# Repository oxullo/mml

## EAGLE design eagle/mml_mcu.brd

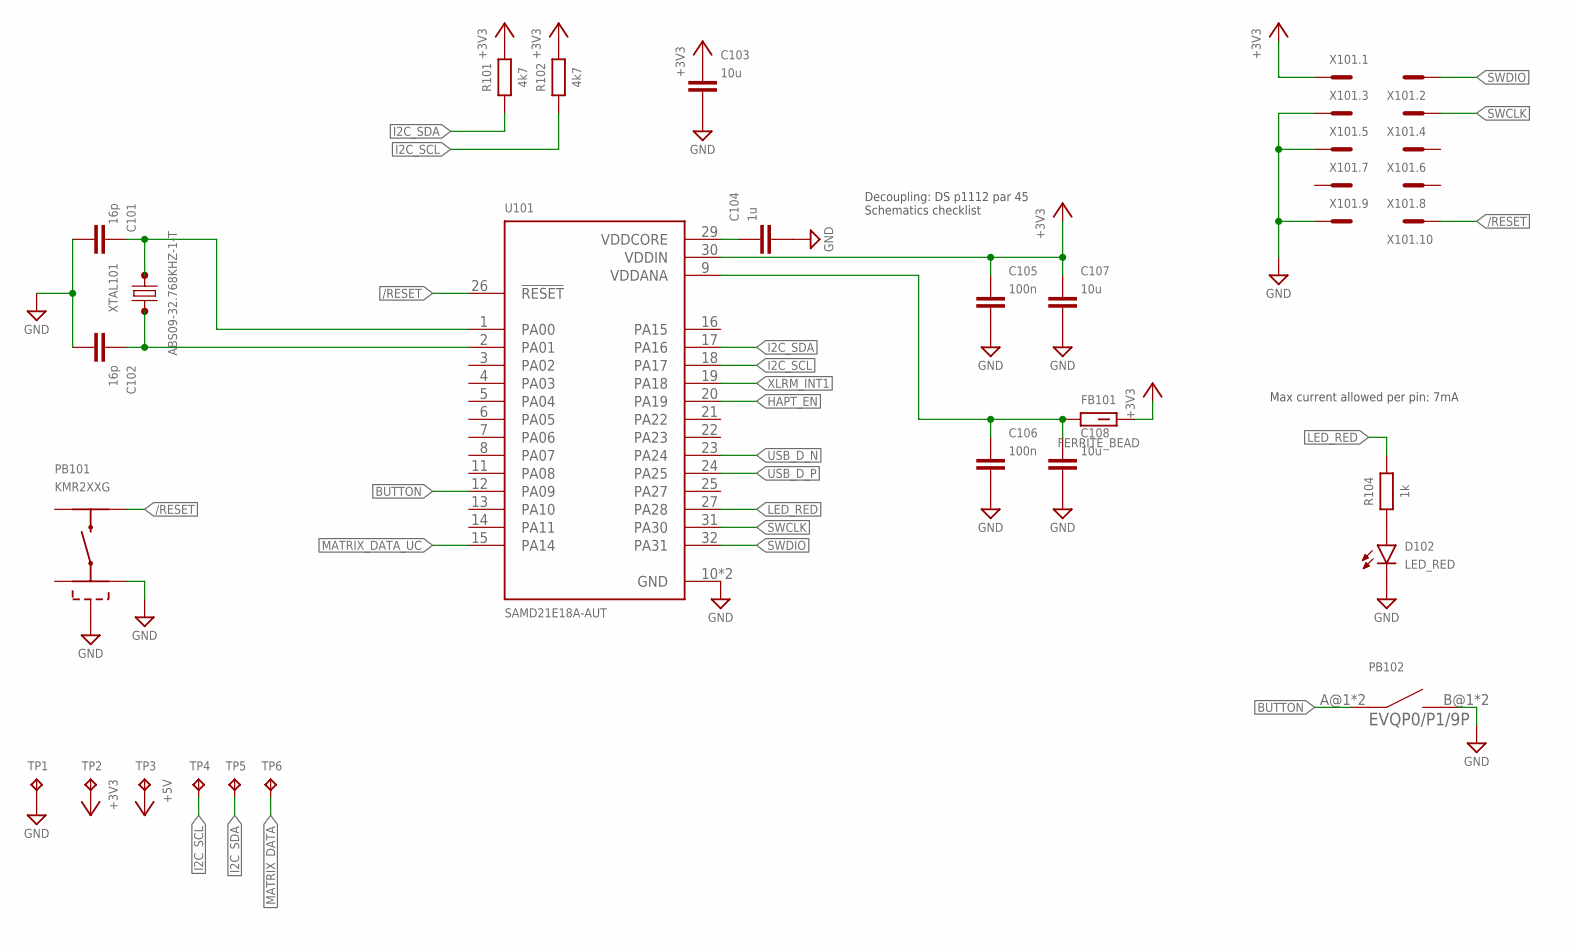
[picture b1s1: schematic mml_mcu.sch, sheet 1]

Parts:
C101, C102: 16p; CAPC1608X85
C103, C107, C108: 10u; CAPC2012X110
C104: 1u; CAPC1608X85
C105, C106: 100n; CAPC1608X85
D102: LED_RED; LEDC2012X110N_FLAT-R
FB101: FERRITE_BEAD; BEADC1608X95N
PB101: KMR2XXG
PB102: EVQP0/P1/9P
R101, R102: 4k7; RESC1608X60
R104: 1k; RESC1608X60
TP1, TP2, TP3, TP4, TP5, TP6: TPTP15R; TP15R
U101: SAMD21E18A-AUT; QFP80P900X900X120-32N
X101: M50-3600542R
XTAL101: ABS09-32.768KHZ-1-T; XTAL410X150X90

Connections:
+3V3: C103.1, C105.1, C107.1, FB101.2, R101.2, R102.2, TP2.TP, U101.30 (VDDIN), X101.1; also elsewhere on the board
+5V: TP3.TP; also elsewhere on the board
/RESET: PB101.1, U101.26 (!RESET), X101.10
BUTTON: PB102.A@1 (A), PB102.A@2 (A), U101.12 (PA09)
GND: C101.2, C102.2, C103.2, C104.2, C105.2, C106.2, C107.2, C108.2, D102.C, PB101.2, PB101.5, PB102.B@1 (B), PB102.B@2 (B), TP1.TP, U101.10 (GND), U101.28 (GND), X101.3, X101.5, X101.9; also elsewhere on the board
HAPT_EN: U101.20 (PA19); also elsewhere on the board
I2C_SCL: R102.1, TP4.TP, U101.18 (PA17); also elsewhere on the board
I2C_SDA: R101.1, TP5.TP, U101.17 (PA16); also elsewhere on the board
LED_RED: R104.2, U101.27 (PA28)
MATRIX_DATA: TP6.TP; also elsewhere on the board
MATRIX_DATA_UC: U101.15 (PA14); also elsewhere on the board
unnamed: C101.1, U101.1 (PA00), XTAL101.1 (A)
unnamed: C102.1, U101.2 (PA01), XTAL101.2 (B)
unnamed: C104.1, U101.29 (VDDCORE)
unnamed: D102.A, R104.1
unnamed: C106.1, C108.1, FB101.1, U101.9 (VDDANA)
SWCLK: U101.31 (PA30), X101.4
SWDIO: U101.32 (PA31), X101.2
USB_D_N: U101.23 (PA24); also elsewhere on the board
USB_D_P: U101.24 (PA25); also elsewhere on the board
XLRM_INT1: U101.19 (PA18); also elsewhere on the board

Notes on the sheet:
Decoupling: DS p1112 par 45 Schematics checklist
Max current allowed per pin: 7mA

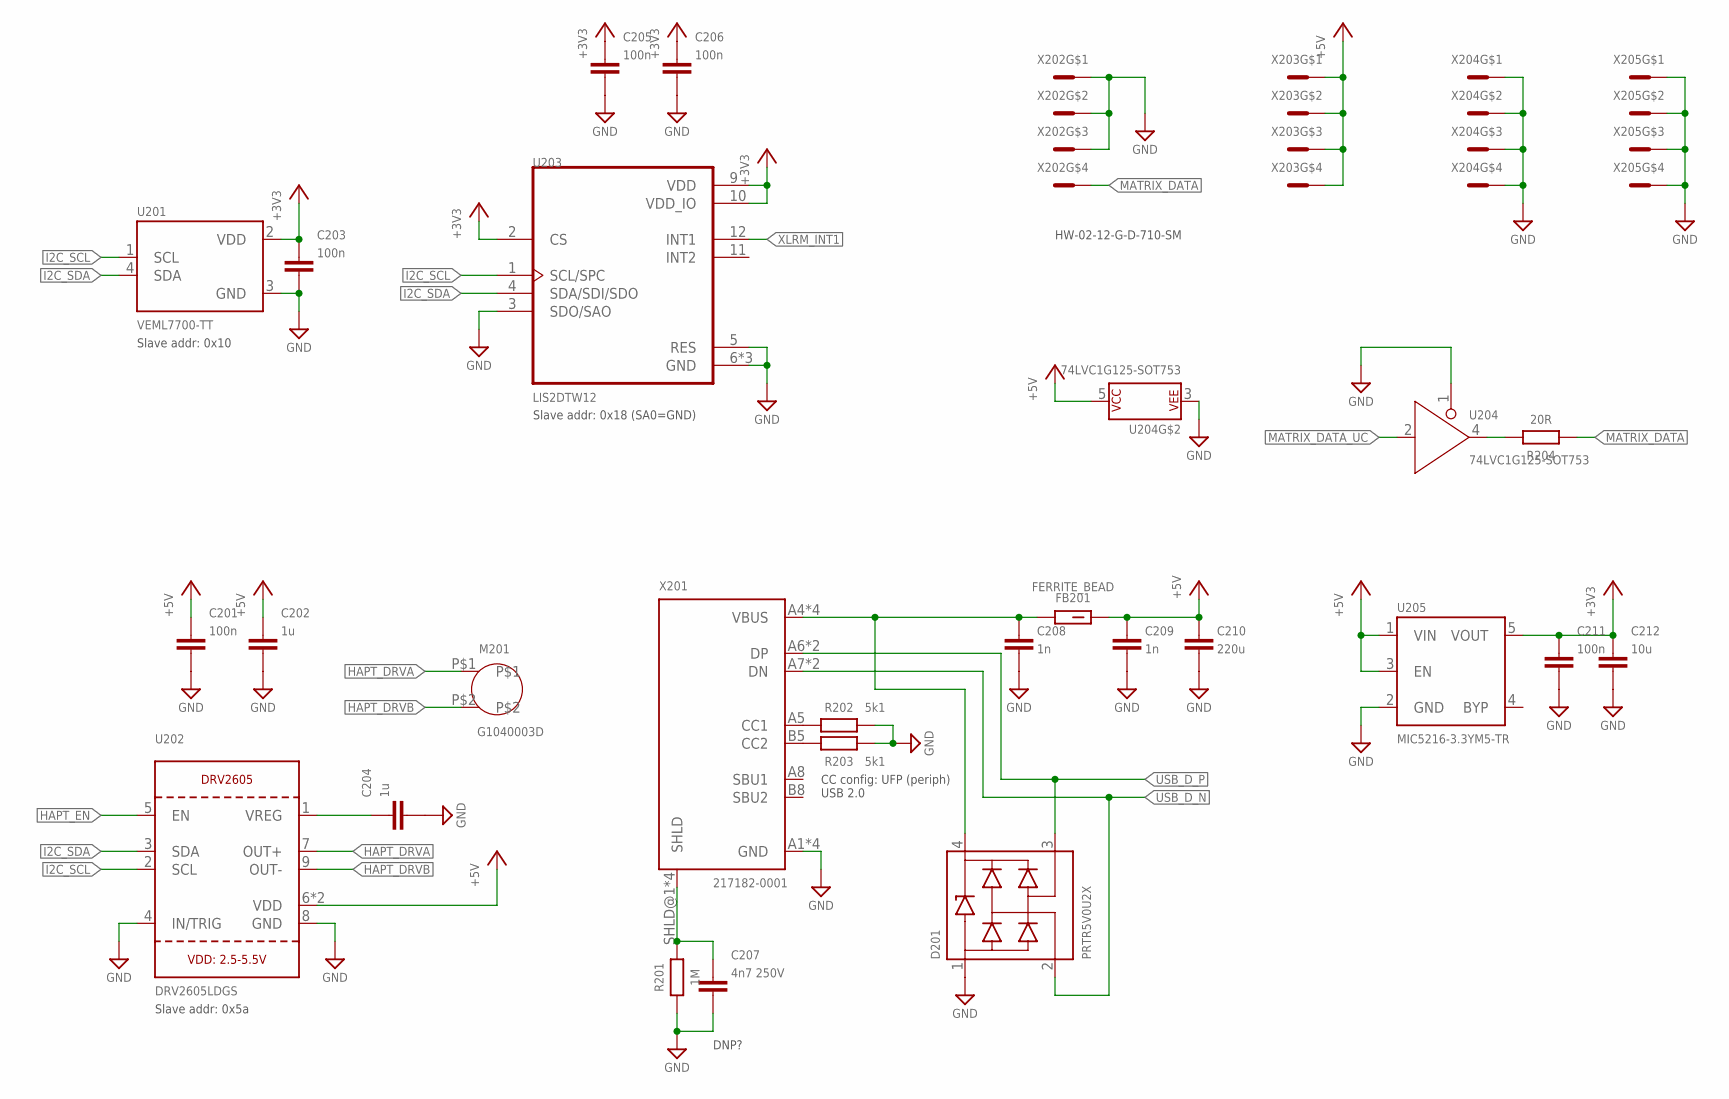
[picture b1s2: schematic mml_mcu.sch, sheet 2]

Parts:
C201, C203, C205, C206, C211: 100n; CAPC1608X85
C202, C204: 1u; CAPC1608X85
C207: 4n7 250V; CAPC1608X85
C208, C209: 1n; CAPC1608X85
C210: 220u; CAPC3216X135
C212: 10u; CAPC2012X110
D201: PRTR5V0U2X; SOT190P230X110-4N
FB201: FERRITE_BEAD; BEADC1608X95N
M201: G1040003D
R201: 1M; RESC1608X60
R202, R203: 5k1; RESC1608X60
R204: 20R; RESC1608X60
U201: VEML7700-TT; XDCR_VEML7700-TT
U202: DRV2605LDGS; PSOP10; LCSC_PART C527464
U203: LIS2DTW12; PQFN50P200X200100-12N; LCSC_PART C110926
U204: 74LVC1G125-SOT753; SOT95P280X145-5N
U205: MIC5216-3.3YM5-TR; SOT95P280X145-5N
X201: 217182-0001
X202, X203, X204, X205: HW-02-10-T-D-500-SM

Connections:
+3V3: C203.1, C205.1, C206.1, C211.1, C212.1, U201.2 (VDD), U203.2 (CS), U203.9 (VDD), U203.10 (VDD_IO), U205.5 (VOUT); also elsewhere on the board
+5V: C201.1, C202.1, C209.1, C210.1, FB201.2, U202.6 (VDD), U202.10 (VDD), U204.5 (P$V+), U205.1 (VIN), U205.3 (EN), X203.P$1, X203.P$2, X203.P$3, X203.P$4; also elsewhere on the board
GND: C201.2, C202.2, C203.2, C204.2, C205.2, C206.2, C207.2, C208.2, C209.2, C210.2, C211.2, C212.2, D201.1, R201.1, R202.1, R203.1, U201.3 (GND), U202.4 (IN/TRIG), U202.8 (GND), U203.3 (SDO/SAO), U203.5 (RES), U203.6 (GND), U203.7 (GND), U203.8 (GND), U204.1 (/OE), U204.3 (P$V-), U205.2 (GND), X201.A1 (GND), X201.A12 (GND), X201.B1 (GND), X201.B12 (GND), X202.P$1, X202.P$2, X202.P$3, X204.P$1, X204.P$2, X204.P$3, X204.P$4, X205.P$1, X205.P$2, X205.P$3, X205.P$4; also elsewhere on the board
HAPT_DRVA: M201.P$1, U202.7 (OUT+)
HAPT_DRVB: M201.P$2, U202.9 (OUT-)
HAPT_EN: U202.5 (EN); also elsewhere on the board
I2C_SCL: U201.1 (SCL), U202.2 (SCL), U203.1 (SCL/SPC); also elsewhere on the board
I2C_SDA: U201.4 (SDA), U202.3 (SDA), U203.4 (SDA/SDI/SDO); also elsewhere on the board
MATRIX_DATA: R204.1, X202.P$4; also elsewhere on the board
MATRIX_DATA_UC: U204.2 (A); also elsewhere on the board
unnamed: C204.1, U202.1 (VREG)
unnamed: C207.1, R201.2, X201.SHLD@1 (SHLD), X201.SHLD@2 (SHLD), X201.SHLD@3 (SHLD), X201.SHLD@4 (SHLD)
unnamed: C208.1, D201.4, FB201.1, X201.A4 (VBUS), X201.A9 (VBUS), X201.B4 (VBUS), X201.B9 (VBUS)
unnamed: R204.2, U204.4 (Y)
unnamed: R202.2, X201.A5 (CC1)
unnamed: R203.2, X201.B5 (CC2)
USB_D_N: D201.2, X201.A7 (DN), X201.B7 (DN); also elsewhere on the board
USB_D_P: D201.3, X201.A6 (DP), X201.B6 (DP); also elsewhere on the board
XLRM_INT1: U203.12 (INT1); also elsewhere on the board

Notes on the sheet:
Slave addr: 0x18 (SA0=GND)
Slave addr: 0x10
Slave addr: 0x5a
DNP?
CC config: UFP (periph) USB 2.0
HW-02-12-G-D-710-SM

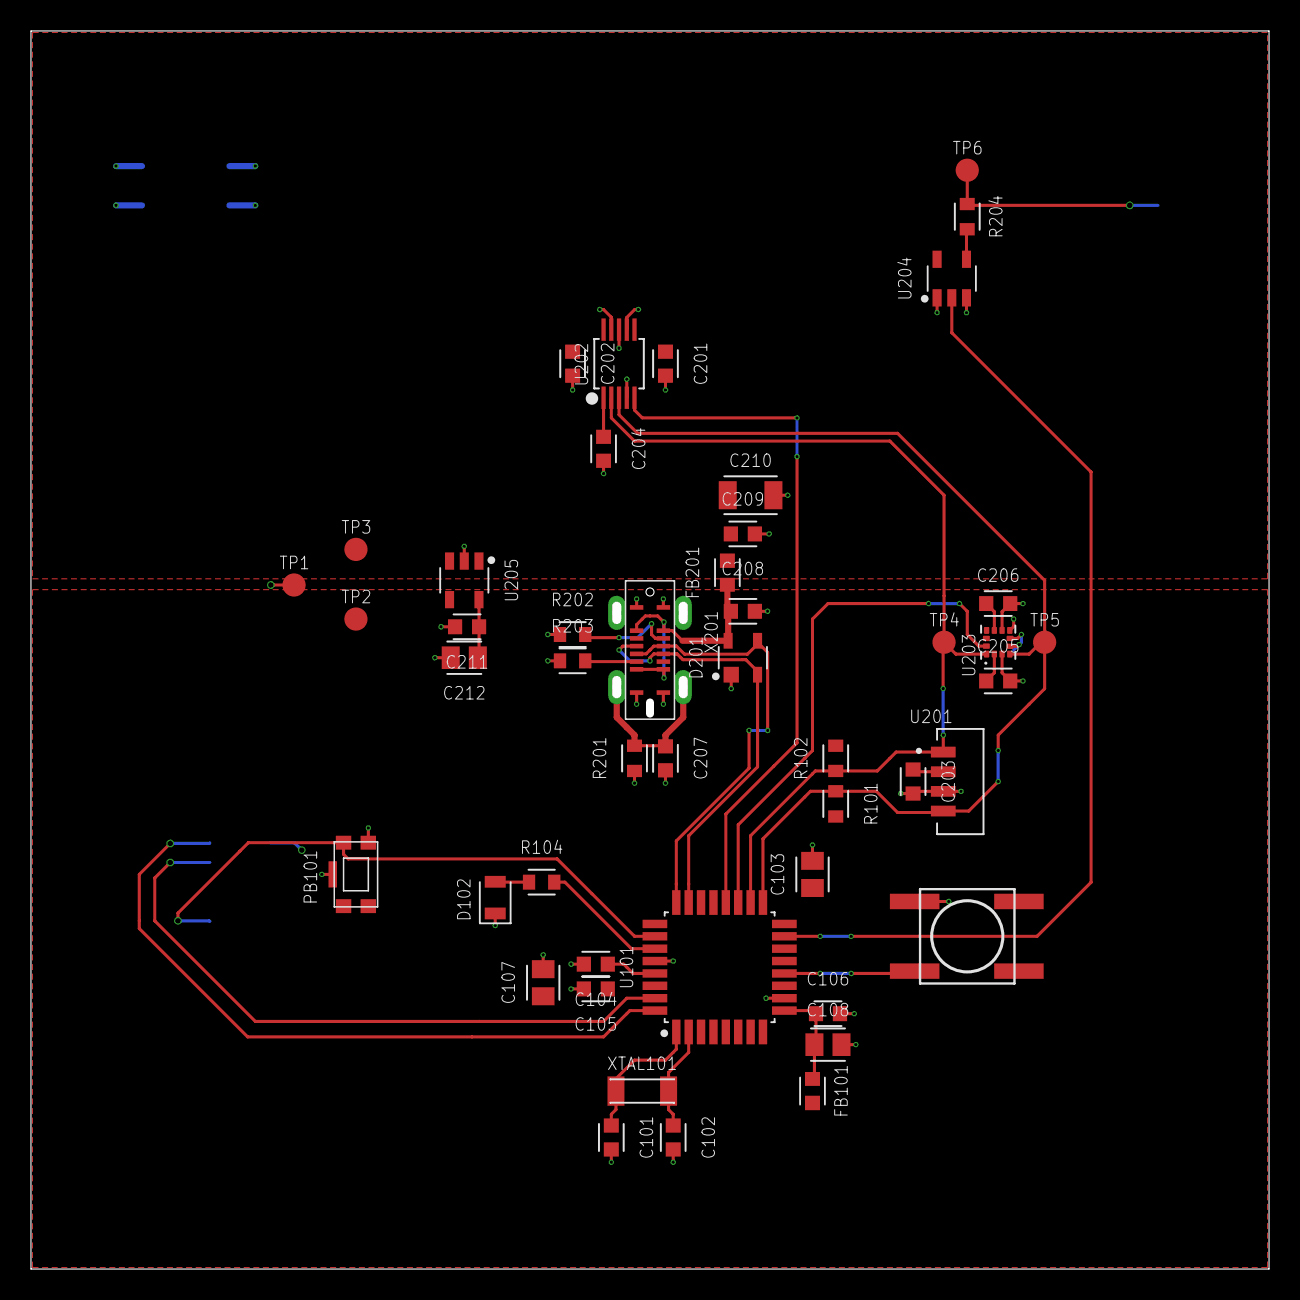
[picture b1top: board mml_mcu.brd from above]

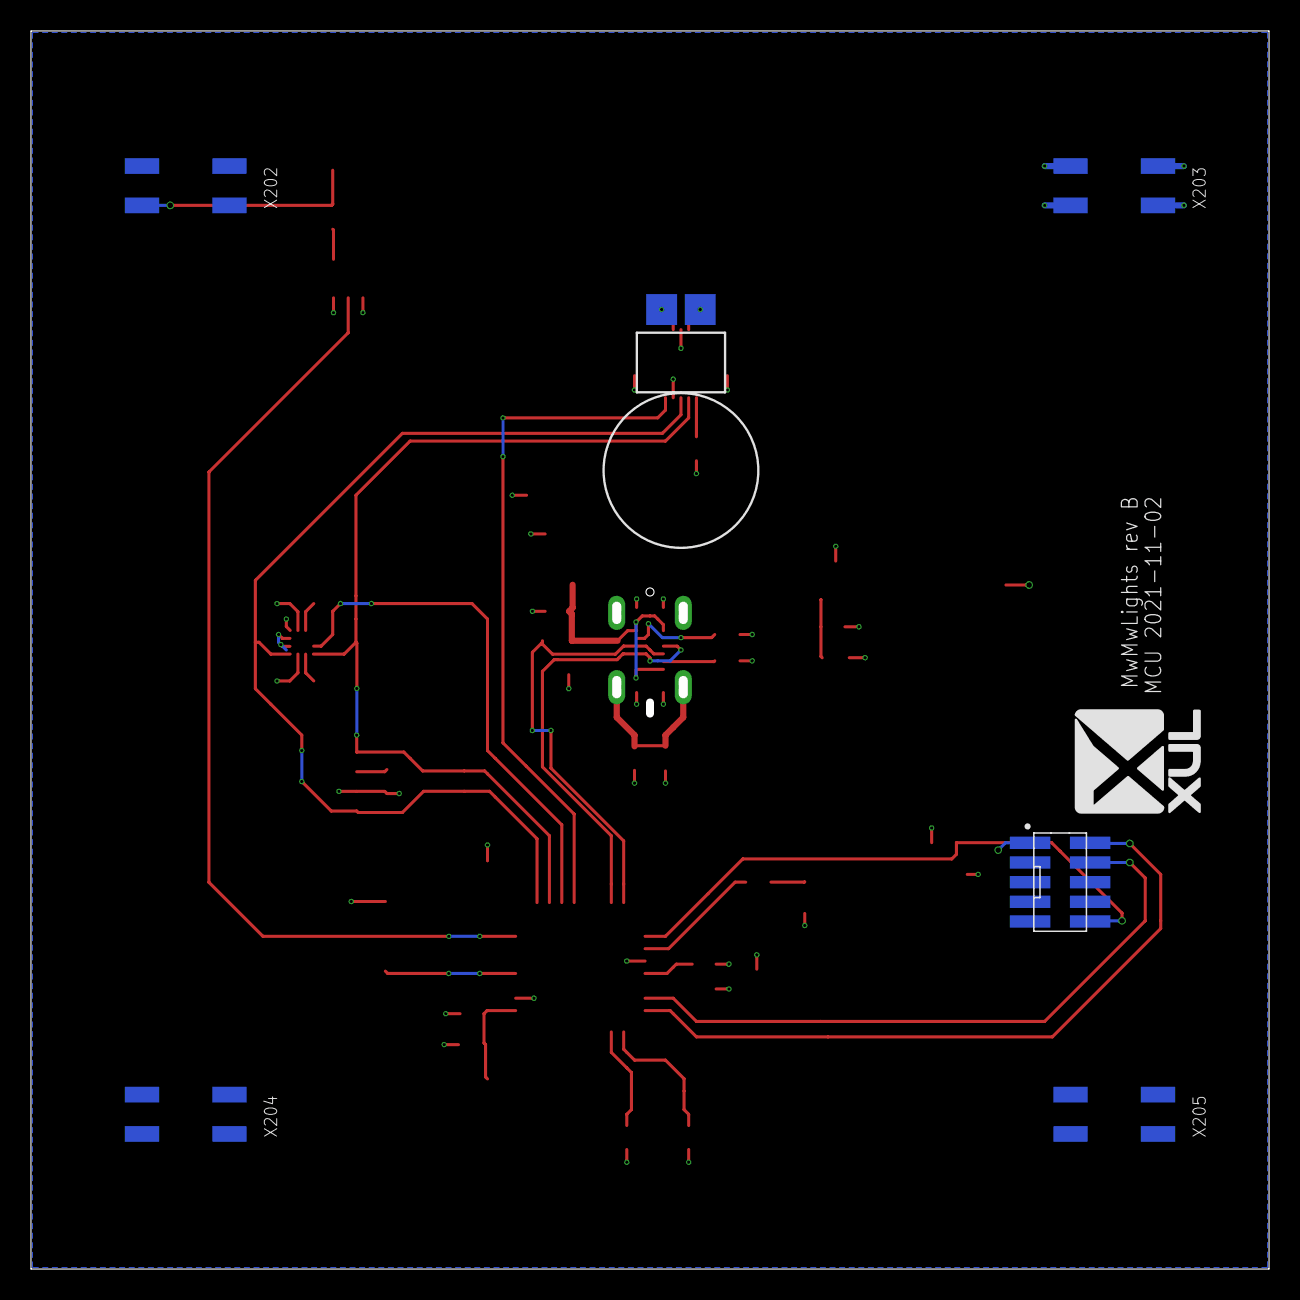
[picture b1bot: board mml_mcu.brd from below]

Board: 2 copper layers, 80.0 x 80.0 mm, 54 parts (7 on the bottom side), 29 nets.

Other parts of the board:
U$1: XUL-LOGO-8MMH

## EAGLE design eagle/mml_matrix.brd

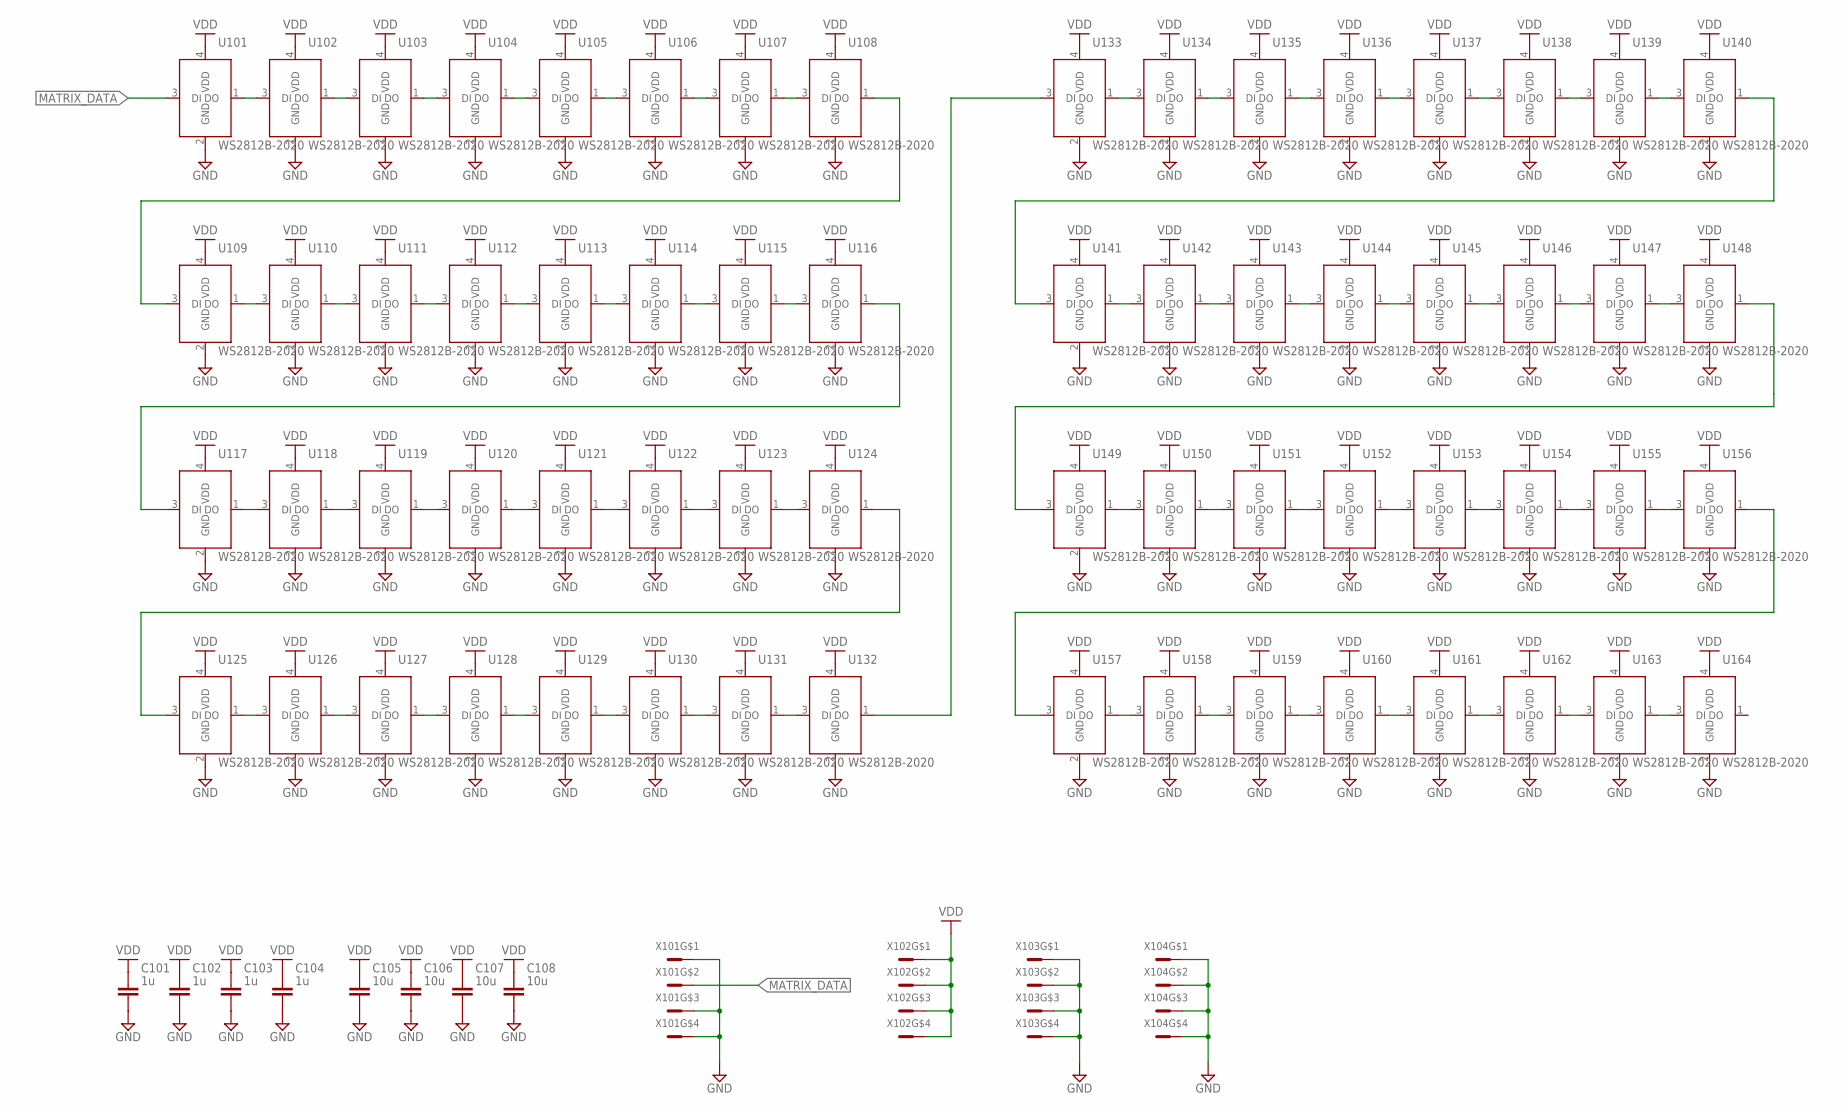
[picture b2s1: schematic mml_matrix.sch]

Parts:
C101, C102, C103, C104: 1u; CAPC1608X85
C105, C106, C107, C108: 10u; CAPC2012X110
U101, U102, U103, U104, U105, U106, U107, U108, U109, U110, U111, U112, U113, U114, U115, U116, U117, U118, U119, U120, U121, U122, U123, U124, U125, U126, U127, U128, U129, U130, U131, U132, U133, U134, U135, U136, U137, U138, U139, U140, U141, U142, U143, U144, U145, U146, U147, U148, U149, U150, U151, U152, U153, U154, U155, U156, U157, U158, U159, U160, U161, U162, U163, U164: WS2812B-2020; RESCAV100P200X220X28-4L
X101, X102, X103, X104: HW-02-10-T-D-500-SM

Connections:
GND: C101.2, C102.2, C103.2, C104.2, C105.2, C106.2, C107.2, C108.2, U101.2 (GND), U102.2 (GND), U103.2 (GND), U104.2 (GND), U105.2 (GND), U106.2 (GND), U107.2 (GND), U108.2 (GND), U109.2 (GND), U110.2 (GND), U111.2 (GND), U112.2 (GND), U113.2 (GND), U114.2 (GND), U115.2 (GND), U116.2 (GND), U117.2 (GND), U118.2 (GND), U119.2 (GND), U120.2 (GND), U121.2 (GND), U122.2 (GND), U123.2 (GND), U124.2 (GND), U125.2 (GND), U126.2 (GND), U127.2 (GND), U128.2 (GND), U129.2 (GND), U130.2 (GND), U131.2 (GND), U132.2 (GND), U133.2 (GND), U134.2 (GND), U135.2 (GND), U136.2 (GND), U137.2 (GND), U138.2 (GND), U139.2 (GND), U140.2 (GND), U141.2 (GND), U142.2 (GND), U143.2 (GND), U144.2 (GND), U145.2 (GND), U146.2 (GND), U147.2 (GND), U148.2 (GND), U149.2 (GND), U150.2 (GND), U151.2 (GND), U152.2 (GND), U153.2 (GND), U154.2 (GND), U155.2 (GND), U156.2 (GND), U157.2 (GND), U158.2 (GND), U159.2 (GND), U160.2 (GND), U161.2 (GND), U162.2 (GND), U163.2 (GND), U164.2 (GND), X101.P$1, X101.P$3, X101.P$4, X103.P$1, X103.P$2, X103.P$3, X103.P$4, X104.P$1, X104.P$2, X104.P$3, X104.P$4
MATRIX_DATA: U101.3 (DI), X101.P$2
unnamed: U101.1 (DO), U102.3 (DI)
unnamed: U102.1 (DO), U103.3 (DI)
unnamed: U103.1 (DO), U104.3 (DI)
unnamed: U104.1 (DO), U105.3 (DI)
unnamed: U105.1 (DO), U106.3 (DI)
unnamed: U106.1 (DO), U107.3 (DI)
unnamed: U107.1 (DO), U108.3 (DI)
unnamed: U117.1 (DO), U118.3 (DI)
unnamed: U118.1 (DO), U119.3 (DI)
unnamed: U119.1 (DO), U120.3 (DI)
unnamed: U120.1 (DO), U121.3 (DI)
unnamed: U121.1 (DO), U122.3 (DI)
unnamed: U122.1 (DO), U123.3 (DI)
unnamed: U123.1 (DO), U124.3 (DI)
unnamed: U133.1 (DO), U134.3 (DI)
unnamed: U134.1 (DO), U135.3 (DI)
unnamed: U135.1 (DO), U136.3 (DI)
unnamed: U136.1 (DO), U137.3 (DI)
unnamed: U137.1 (DO), U138.3 (DI)
unnamed: U138.1 (DO), U139.3 (DI)
unnamed: U139.1 (DO), U140.3 (DI)
unnamed: U149.1 (DO), U150.3 (DI)
unnamed: U150.1 (DO), U151.3 (DI)
unnamed: U151.1 (DO), U152.3 (DI)
unnamed: U152.1 (DO), U153.3 (DI)
unnamed: U153.1 (DO), U154.3 (DI)
unnamed: U154.1 (DO), U155.3 (DI)
unnamed: U155.1 (DO), U156.3 (DI)
unnamed: U109.1 (DO), U110.3 (DI)
unnamed: U110.1 (DO), U111.3 (DI)
unnamed: U111.1 (DO), U112.3 (DI)
unnamed: U112.1 (DO), U113.3 (DI)
unnamed: U113.1 (DO), U114.3 (DI)
unnamed: U114.1 (DO), U115.3 (DI)
unnamed: U115.1 (DO), U116.3 (DI)
unnamed: U125.1 (DO), U126.3 (DI)
unnamed: U126.1 (DO), U127.3 (DI)
unnamed: U127.1 (DO), U128.3 (DI)
unnamed: U128.1 (DO), U129.3 (DI)
unnamed: U129.1 (DO), U130.3 (DI)
unnamed: U130.1 (DO), U131.3 (DI)
unnamed: U131.1 (DO), U132.3 (DI)
unnamed: U141.1 (DO), U142.3 (DI)
unnamed: U142.1 (DO), U143.3 (DI)
unnamed: U143.1 (DO), U144.3 (DI)
unnamed: U144.1 (DO), U145.3 (DI)
unnamed: U145.1 (DO), U146.3 (DI)
unnamed: U146.1 (DO), U147.3 (DI)
unnamed: U147.1 (DO), U148.3 (DI)
unnamed: U157.1 (DO), U158.3 (DI)
unnamed: U158.1 (DO), U159.3 (DI)
unnamed: U159.1 (DO), U160.3 (DI)
unnamed: U160.1 (DO), U161.3 (DI)
unnamed: U161.1 (DO), U162.3 (DI)
unnamed: U162.1 (DO), U163.3 (DI)
unnamed: U163.1 (DO), U164.3 (DI)
unnamed: U108.1 (DO), U109.3 (DI)
unnamed: U116.1 (DO), U117.3 (DI)
unnamed: U124.1 (DO), U125.3 (DI)
unnamed: U132.1 (DO), U133.3 (DI)
unnamed: U140.1 (DO), U141.3 (DI)
unnamed: U148.1 (DO), U149.3 (DI)
unnamed: U156.1 (DO), U157.3 (DI)
VDD: C101.1, C102.1, C103.1, C104.1, C105.1, C106.1, C107.1, C108.1, U101.4 (VDD), U102.4 (VDD), U103.4 (VDD), U104.4 (VDD), U105.4 (VDD), U106.4 (VDD), U107.4 (VDD), U108.4 (VDD), U109.4 (VDD), U110.4 (VDD), U111.4 (VDD), U112.4 (VDD), U113.4 (VDD), U114.4 (VDD), U115.4 (VDD), U116.4 (VDD), U117.4 (VDD), U118.4 (VDD), U119.4 (VDD), U120.4 (VDD), U121.4 (VDD), U122.4 (VDD), U123.4 (VDD), U124.4 (VDD), U125.4 (VDD), U126.4 (VDD), U127.4 (VDD), U128.4 (VDD), U129.4 (VDD), U130.4 (VDD), U131.4 (VDD), U132.4 (VDD), U133.4 (VDD), U134.4 (VDD), U135.4 (VDD), U136.4 (VDD), U137.4 (VDD), U138.4 (VDD), U139.4 (VDD), U140.4 (VDD), U141.4 (VDD), U142.4 (VDD), U143.4 (VDD), U144.4 (VDD), U145.4 (VDD), U146.4 (VDD), U147.4 (VDD), U148.4 (VDD), U149.4 (VDD), U150.4 (VDD), U151.4 (VDD), U152.4 (VDD), U153.4 (VDD), U154.4 (VDD), U155.4 (VDD), U156.4 (VDD), U157.4 (VDD), U158.4 (VDD), U159.4 (VDD), U160.4 (VDD), U161.4 (VDD), U162.4 (VDD), U163.4 (VDD), U164.4 (VDD), X102.P$1, X102.P$2, X102.P$3, X102.P$4

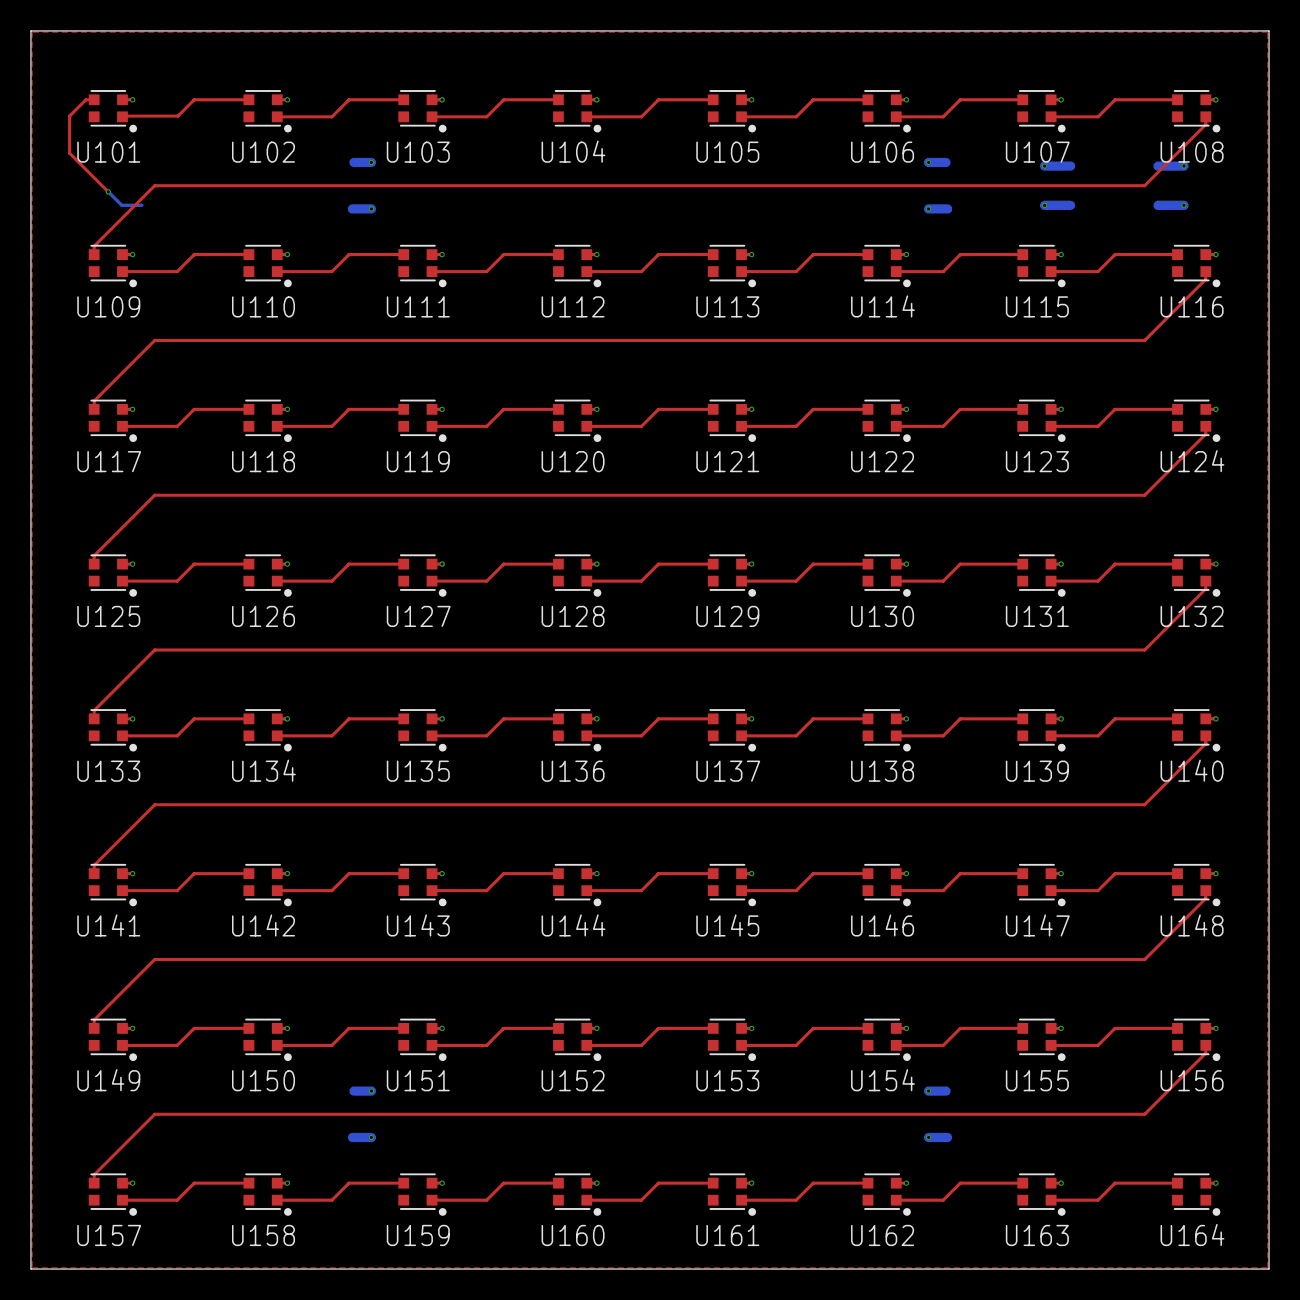
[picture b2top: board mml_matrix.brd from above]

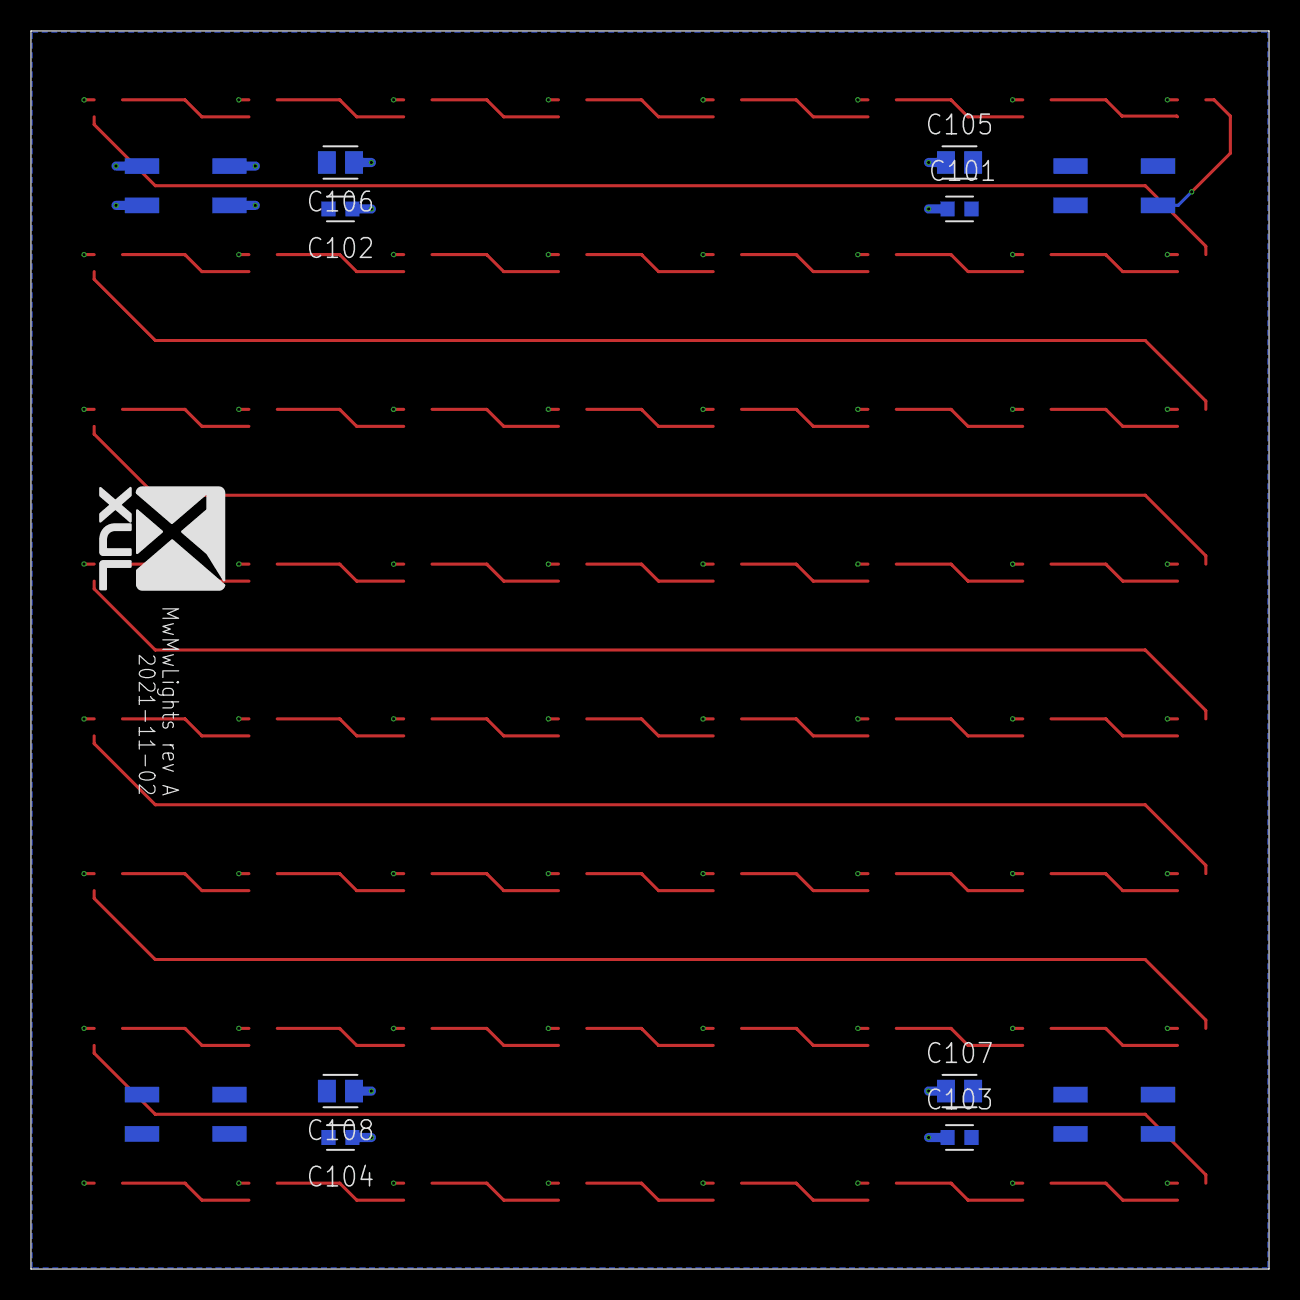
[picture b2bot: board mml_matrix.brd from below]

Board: 2 copper layers, 80.0 x 80.0 mm, 77 parts (13 on the bottom side), 66 nets.

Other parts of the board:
U$1: XUL-LOGO-8MMH

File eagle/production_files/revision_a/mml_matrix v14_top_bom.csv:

Comment,Designator,Footprint,LCSC Part #
WS2812B-2020,U101 U102 U103 U104 U105 U106 U107 U108 U109 U110 U111 U112 U113 U114 U115 U116 U117 U118 U119 U120 U121 U122 U123 U124 U125 U126 U127 U128 U129 U130 U131 U132 U133 U134 U135 U136 U137 U138 U139 U140 U141 U142 U143 U144 U145 U146 U147 U148 U149 U150 U151 U152 U153 U154 U155 U156 U157 U158 U159 U160 U161 U162 U163 U164,RESCAV100P200X220X28-4L,

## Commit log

2021-10-18 Initial import for revision A
2021-10-18 Add production files for revision A
2021-10-18 Add literature
2021-10-18 Add implementation test for the accelerometer
2021-10-18 Add a minimal test for the haptic driver
2021-10-18 Add gitignores
2021-10-19 Add tester for VEML7700
2021-10-23 Add blink experiment
2021-10-23 Add i2c scanner
2021-10-23 Adapt VEML7700 test for MML
2021-10-23 Add a matrix test
2021-10-24 Adapt for mml and fix missing wire init
2021-10-25 Initial import of the firmware
2021-10-25 Add board bootloader
2021-10-25 Integrate LIS2DTW
2021-10-25 Integrate haptic driver
2021-10-25 Integrate fastled
2021-10-25 Integrate orientation manager (draft)
2021-10-25 Extract config constants
2021-10-25 Implement orientation detection and change report
2021-10-25 Add animators
2021-10-25 Expose acceleration data
2021-10-25 Add the last two animators
2021-10-25 Refactor haptics hardware into a singleton
2021-10-25 Add haptic feedback to the rain animation
2021-10-25 Switch tilt thresholds to normalised coordinates
2021-10-27 Add pdf dumps for rev A
2021-10-28 Add haptic feedback to the ball game, increasing bounciness
2021-10-28 Add heart animation
2021-10-28 Add simple hue shift
2021-11-15 Add cam file for jlcpcb
2021-11-15 MCU board revision B

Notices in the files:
parts and their libraries:
microbuilder: This work is placed in the public domain, and may be freely used for commercial and non-commercial work with the following conditions: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
